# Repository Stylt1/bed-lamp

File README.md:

# bed-lamp
Smart bed lamp to optimise sleep quality.

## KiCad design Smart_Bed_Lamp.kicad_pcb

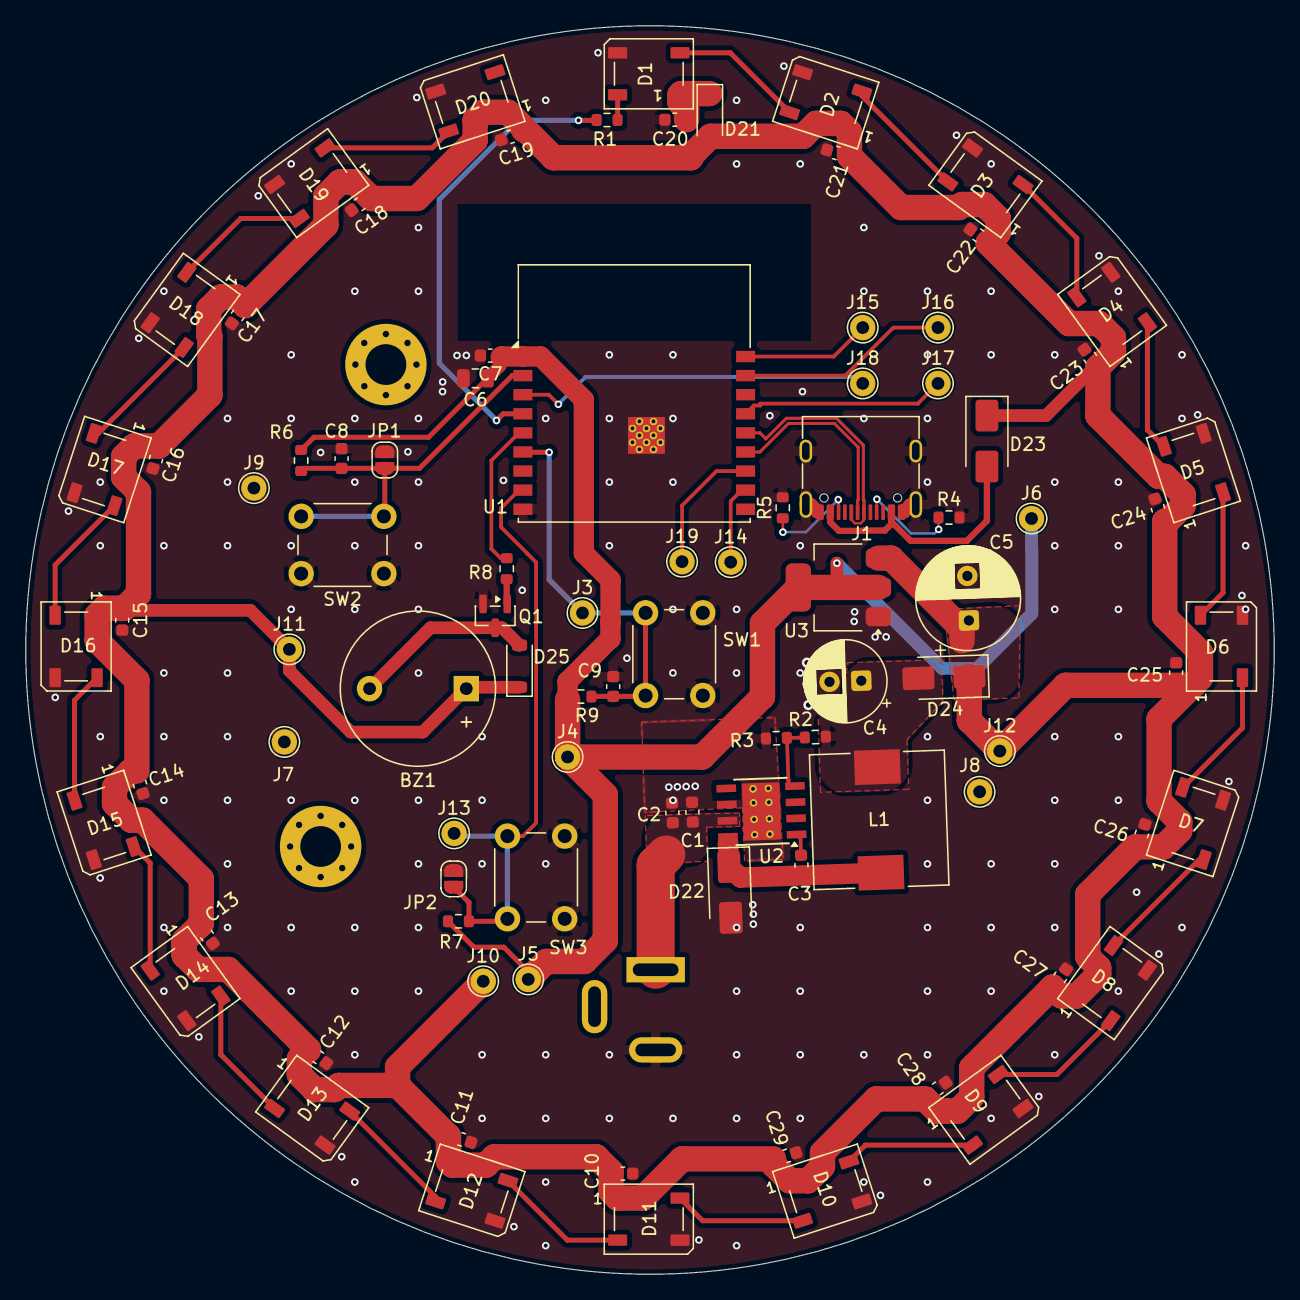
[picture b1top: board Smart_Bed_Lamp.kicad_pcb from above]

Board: 2 copper layers, 98.1 x 98.1 mm, 93 parts (1 on the bottom side), 47 nets.

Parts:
BZ1: Passive; Buzzer_12x9.5RM7.6
C1, C2: 4,7uF; C_0603_1608Metric
C3: 0,01uF; C_0603_1608Metric
C4: 220uF; CP_Radial_D6.3mm_P2.50mm
C5: 470uF; CP_Radial_D8.0mm_P3.50mm
C6: 10uF; C_0805_2012Metric
C7, C9, C10, C11, C12, C13, C14, C15, C16, C17, C18, C19, C20, C21, C22, C23, C24, C25, C26, C27, C28, C29: 100nF; C_0603_1608Metric
C8: 1uF; C_0603_1608Metric
D1, D2, D3, D4, D5, D6, D7, D8, D9, D10, D11, D12, D13, D14, D15, D16, D17, D18, D19, D20: WS2812B; LED_WS2812B_PLCC4_5.0x5.0mm_P3.2mm
D21, D25: 1N4148W; D_SOD-123
D22, D23, D24: SS34; D_SMA
J1: USB_C_Receptacle_USB2.0_14P; USB_C_Receptacle_G-Switch_GT-USB-7010ASV
J2: Barrel_Jack; BarrelJack_GCT_DCJ200-10-A_Horizontal
J3: IO7; TestPoint_THTPad_D2.0mm_Drill1.0mm
J4, J5, J6: 3V3; TestPoint_THTPad_D2.0mm_Drill1.0mm
J7, J8, J9: GND; TestPoint_THTPad_D2.0mm_Drill1.0mm
J10, J11, J12: 5V; TestPoint_THTPad_D2.0mm_Drill1.0mm
J13: BOOT; TestPoint_THTPad_D2.0mm_Drill1.0mm
J14: RX; TestPoint_THTPad_D2.0mm_Drill1.0mm
J15: IO0; TestPoint_THTPad_D2.0mm_Drill1.0mm
J16: IO1; TestPoint_THTPad_D2.0mm_Drill1.0mm
J17: IO3; TestPoint_THTPad_D2.0mm_Drill1.0mm
J18: IO4; TestPoint_THTPad_D2.0mm_Drill1.0mm
J19: TX; TestPoint_THTPad_D2.0mm_Drill1.0mm
JP1: RST; SolderJumper-2_P1.3mm_Open_RoundedPad1.0x1.5mm
JP2: BOOT; SolderJumper-2_P1.3mm_Open_RoundedPad1.0x1.5mm
L1: 22uH; L_10.4x10.4_H4.8
Q1: MMBT3904; SOT-23
R1: 330R; R_0603_1608Metric
R2, R6, R7, R9: 10K; R_0603_1608Metric
R3: 3,24K; R_0603_1608Metric
R4, R5: 5K1; R_0603_1608Metric
R8: 1K; R_0603_1608Metric
SW1: SW_Push; SW_PUSH_6mm
SW2: RST; SW_PUSH_6mm
SW3: BOOT; SW_PUSH_6mm
U1: ESP32-C3-WROOM-02
U2: TPS5430DDA; TI_SO-PowerPAD-8_ThermalVias
U3: AMS1117-3.3; SOT-223-3_TabPin2

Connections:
/Schematic/3V3: C6.1, C7.1, J4.1 (Pin_1_1), J5.1 (Pin_1_1), J6.1 (Pin_1_1), R6.1, R7.1, R9.1, U1.1 (3V3), U3.2 (VO)
/Schematic/5V: BZ1.1 (+), C5.1, C10.1, C11.1, C12.1, C13.1, C14.1, C15.1, C16.1, C17.1, C18.1, C19.1, C21.1, C22.1, C23.1, C24.1, C25.1, C26.1, C27.1, C28.1, C29.1, D2.1 (VDD), D3.1 (VDD), D4.1 (VDD), D5.1 (VDD), D6.1 (VDD), D7.1 (VDD), D8.1 (VDD), D9.1 (VDD), D10.1 (VDD), D11.1 (VDD), D12.1 (VDD), D13.1 (VDD), D14.1 (VDD), D15.1 (VDD), D16.1 (VDD), D17.1 (VDD), D18.1 (VDD), D19.1 (VDD), D20.1 (VDD), D21.2 (A), D23.1 (K), D24.1 (K), D25.1 (K), J10.1 (Pin_1_1), J11.1 (Pin_1_1), J12.1 (Pin_1_1), U3.3 (VI)
/Schematic/BZ: R8.2, U1.5 (IO6)
/Schematic/D+: J1.A6 (D+), J1.B6 (D+), U1.14 (IO19)
/Schematic/D-: J1.A7 (D-), J1.B7 (D-), U1.13 (IO18)
/Schematic/DC_IN: C1.2, C2.2, J2.1, U2.7 (VIN)
/Schematic/DIN: R1.1, U1.4 (IO5)
/Schematic/DOUT_br: D10.2 (DOUT), D11.4 (DIN)
/Schematic/IO0: J15.1 (Pin_1_1), U1.18 (IO0)
/Schematic/IO1: J16.1 (Pin_1_1), U1.17 (IO1)
/Schematic/IO3: J17.1 (Pin_1_1), U1.15 (IO3)
/Schematic/IO4: J18.1 (Pin_1_1), U1.3 (IO4)
GND: C1.1, C2.1, C4.2, C5.2, C6.2, C7.2, C8.2, C9.2, C10.2, C11.2, C12.2, C13.2, C14.2, C15.2, C16.2, C17.2, C18.2, C19.2, C20.2, C21.2, C22.2, C23.2, C24.2, C25.2, C26.2, C27.2, C28.2, C29.2, D1.3 (VSS), D2.3 (VSS), D3.3 (VSS), D4.3 (VSS), D5.3 (VSS), D6.3 (VSS), D7.3 (VSS), D8.3 (VSS), D9.3 (VSS), D10.3 (VSS), D11.3 (VSS), D12.3 (VSS), D13.3 (VSS), D14.3 (VSS), D15.3 (VSS), D16.3 (VSS), D17.3 (VSS), D18.3 (VSS), D19.3 (VSS), D20.3 (VSS), D22.2 (A), J1.A1 (GND), J1.A12 (GND), J1.B1 (GND), J1.B12 (GND), J1.SH (SHIELD), J2.2, J7.1 (Pin_1_1), J8.1 (Pin_1_1), J9.1 (Pin_1_1), JP1.2 (B), JP2.2 (B), Q1.2 (E), R3.2, R4.2, R5.2, SW1.1, SW2.1, SW3.1, U1.9 (GND), U1.19 (GND), U2.6 (GND), U2.9 (GNDPAD), U3.1 (GND)
unnamed: BZ1.2 (-), D25.2 (A), Q1.3 (C)
unnamed: D1.4 (DIN), R1.2
unnamed: D1.2 (DOUT), D2.4 (DIN)
unnamed: C20.1, D1.1 (VDD), D21.1 (K)
unnamed: D2.2 (DOUT), D3.4 (DIN)
unnamed: D3.2 (DOUT), D4.4 (DIN)
unnamed: D4.2 (DOUT), D5.4 (DIN)
unnamed: D5.2 (DOUT), D6.4 (DIN)
unnamed: D6.2 (DOUT), D7.4 (DIN)
unnamed: D7.2 (DOUT), D8.4 (DIN)
unnamed: D8.2 (DOUT), D9.4 (DIN)
unnamed: D9.2 (DOUT), D10.4 (DIN)
unnamed: D11.2 (DOUT), D12.4 (DIN)
unnamed: D12.2 (DOUT), D13.4 (DIN)
unnamed: D13.2 (DOUT), D14.4 (DIN)
unnamed: D14.2 (DOUT), D15.4 (DIN)
unnamed: D15.2 (DOUT), D16.4 (DIN)
unnamed: D16.2 (DOUT), D17.4 (DIN)
unnamed: D17.2 (DOUT), D18.4 (DIN)
unnamed: D18.2 (DOUT), D19.4 (DIN)
unnamed: D19.2 (DOUT), D20.4 (DIN)
unnamed: C3.1, D22.1 (K), L1.1, U2.8 (PH)
unnamed: D23.2 (A), J1.A4 (VBUS), J1.A9 (VBUS), J1.B4 (VBUS), J1.B9 (VBUS)
unnamed: C4.1, D24.2 (A), L1.2, R2.1
unnamed: J1.A5 (CC1), R4.1
unnamed: J1.B5 (CC2), R5.1
unnamed: C9.1, J3.1 (Pin_1_1), R9.2, SW1.2, U1.6 (IO7)
unnamed: J13.1 (Pin_1_1), JP2.1 (A), R7.2, SW3.2, U1.8 (IO9)
unnamed: J14.1 (Pin_1_1), U1.11 (IO20/RXD)
unnamed: J19.1 (Pin_1_1), U1.12 (IO21/TXD)
unnamed: C8.1, JP1.1 (A), R6.2, SW2.2, U1.2 (EN)
unnamed: Q1.1 (B), R8.1
unnamed: C3.2, U2.1 (BOOT)
unnamed: R2.2, R3.1, U2.4 (VSENSE)
